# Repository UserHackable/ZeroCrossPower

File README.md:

## Zero Crossing Detector and Power Supply

I used this board in my Range Rebuild to give me zero crossing detection, as well as provide power using a simple AC wall wart style transformer, and a linear regulator. 

This allows me to drive my solid state relays at zero crossing, and use the inherent frequency of the power line as the clock for a very slow PWM for power control. 

## ZeroCrossPower 

### Board dimensions

* (196851, 122047) original units
* (1.9685, 1.2205) inches
* (50.0002, 30.9999) mm

| Front | Back |
| --- | --- |
|  |  |

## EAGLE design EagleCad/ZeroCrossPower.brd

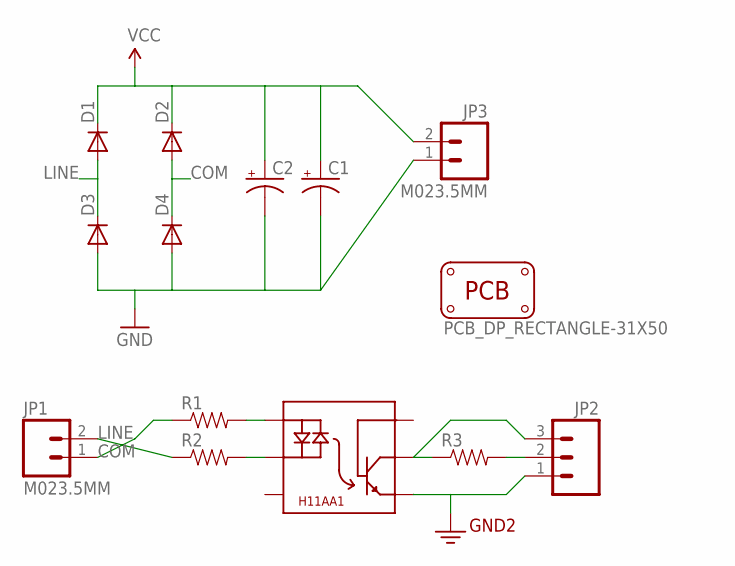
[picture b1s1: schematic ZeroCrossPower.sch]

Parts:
C1: CAP_POLPTH3; CPOL-RADIAL-1000UF-63V
C2: CAP_POLPTH4; CPOL-RADIAL-1000UF-25V
D1, D2, D3, D4: DIODE; DIODE-1N4001-KIT
JP1, JP3: M023.5MM; SCREWTERMINAL-3.5MM-2
JP2: M03PTH; 1X03
PCB1: PCB_DP_RECTANGLE-31X50; DP5031_V1
R1, R2, R3: RESISTORAXIAL-0.3; AXIAL-0.3
U$1: H11AA1; DIP6

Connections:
3.3V: JP2.1, U$1.4 (E)
AC: R1.P$2 (2), U$1.1 (A/C)
CA: R2.P$2 (2), U$1.2 (C/A)
COM: D2.A, D4.C, JP1.2, R2.P$1 (1)
GND: C1.2 (-), C2.2 (-), D3.A, D4.A, JP3.1
LINE: D1.A, D3.C, JP1.1, R1.P$1 (1)
unnamed: JP2.2, R3.P$2 (2)
unnamed: JP2.3, R3.P$1 (1), U$1.5 (C)
VCC: C1.1 (+), C2.1 (+), D1.C, D2.C, JP3.2

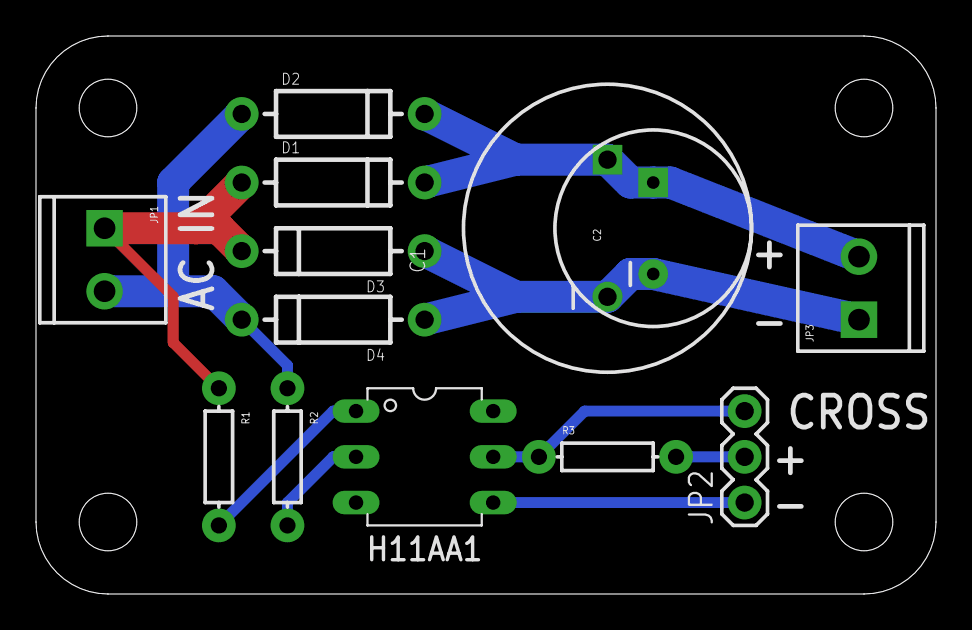
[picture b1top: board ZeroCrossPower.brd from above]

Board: 2 copper layers, 50.0 x 31.0 mm, 14 parts (0 on the bottom side), 9 nets.

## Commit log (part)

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2016-04-08 from Makefile

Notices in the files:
parts and their libraries:
SparkFun-Connectors: Licensing: Creative Commons ShareAlike 4.0 International - https://creativecommons.org/licenses/by-sa/4.0
